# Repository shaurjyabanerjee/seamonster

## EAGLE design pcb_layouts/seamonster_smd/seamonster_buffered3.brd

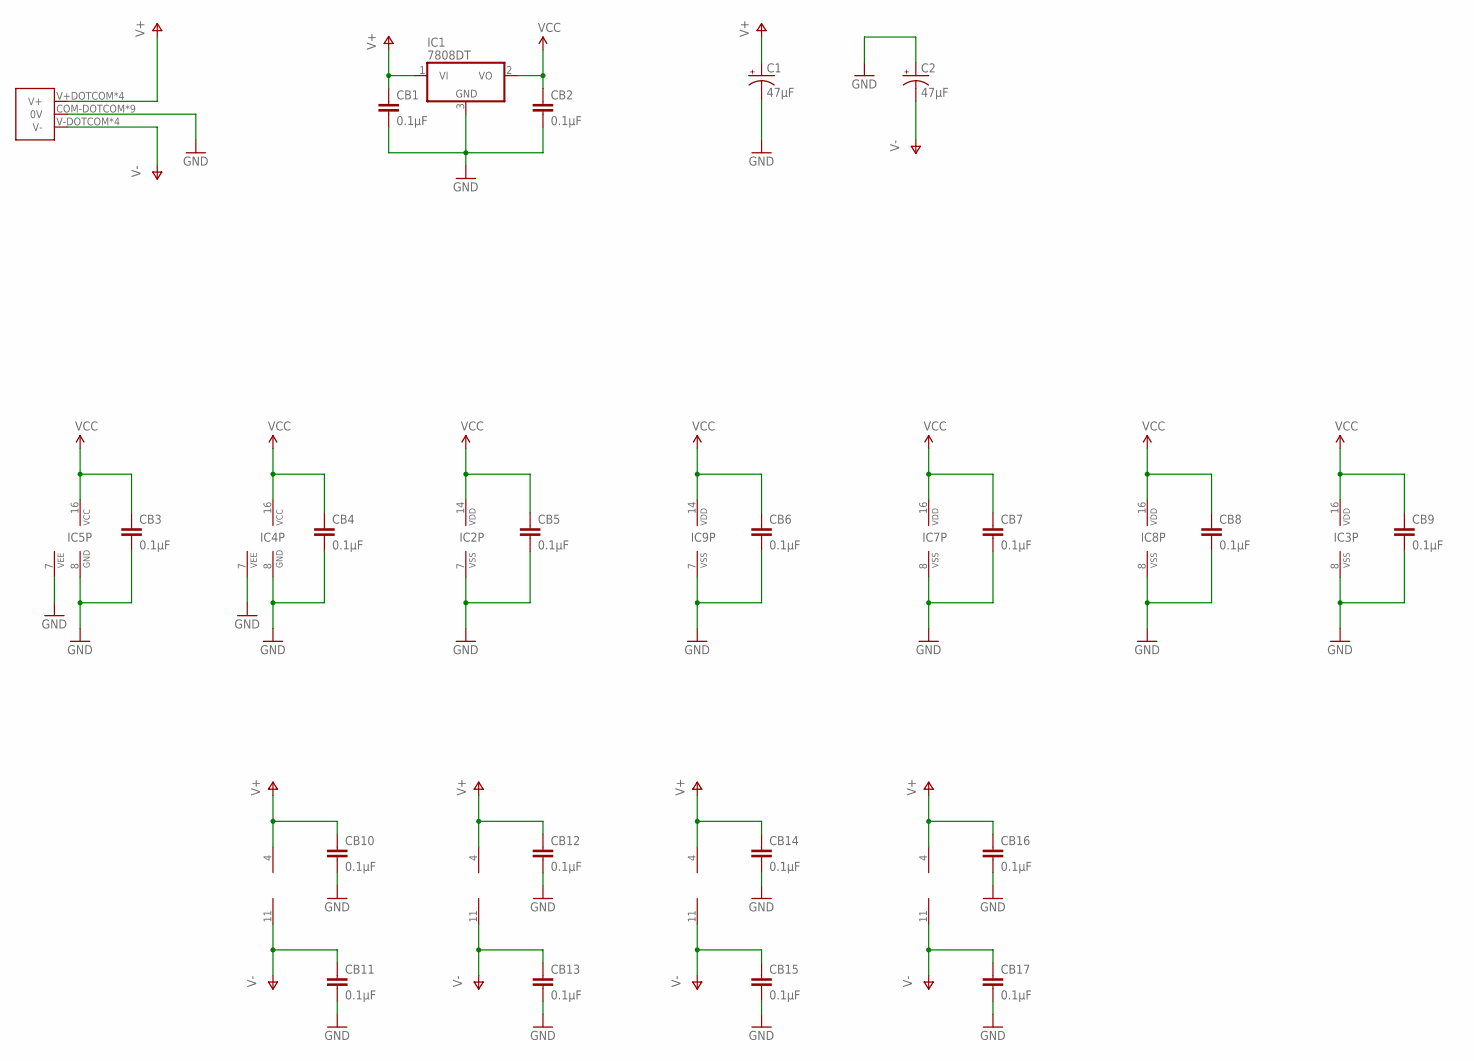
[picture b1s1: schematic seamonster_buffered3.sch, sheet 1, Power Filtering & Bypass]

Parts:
C1, C2: 47µF; CPOL-RADIAL-10UF-25V
CB1, CB2, CB3, CB4, CB5, CB6, CB7, CB8, CB9, CB10, CB11, CB12, CB13, CB14, CB15, CB16, CB17: 0.1µF; 0805
IC1: 7808DT; TO252
IC2: 40106D; SO14
IC3: 4040D; SO16
IC4, IC5: 4051D; SO16
IC7, IC8: 4046D; SO16
IC9: 4070D; SO14
U1, U2, U3: TL084; SO14
U4: TL084D; SO14
U$1: COMBO_POWER

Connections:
GND: C1.2 (-), C2.1 (+), CB1.2, CB2.2, CB3.2, CB4.2, CB5.2, CB6.2, CB7.2, CB8.2, CB9.2, CB10.2, CB11.2, CB12.2, CB13.2, CB14.2, CB15.2, CB16.2, CB17.2, IC1.3 (GND), IC2.7 (VSS), IC3.8 (VSS), IC4.7 (VEE), IC4.8 (GND), IC5.7 (VEE), IC5.8 (GND), IC7.8 (VSS), IC8.8 (VSS), IC9.7 (VSS), U$1.COM-DOTCOM (0V), U$1.COM-EURO1 (0V), U$1.COM-EURO2 (0V), U$1.COM-EURO3 (0V), U$1.COM-EURO4 (0V), U$1.COM-EURO5 (0V), U$1.COM-EURO6 (0V), U$1.COM-MOTM1 (0V), U$1.COM_MOTM2 (0V); also elsewhere on the board
V+: C1.1 (+), CB1.1, CB10.1, CB12.1, CB14.1, CB16.1, IC1.1 (VI), U1.4 (V+), U2.4 (V+), U3.4 (V+), U4.4 (V+), U$1.V+DOTCOM (V+), U$1.V+EURO1 (V+), U$1.V+EURO2 (V+), U$1.V+MOTM (V+); also elsewhere on the board
V-: C2.2 (-), CB11.1, CB13.1, CB15.1, CB17.1, U1.11 (V-), U2.11 (V-), U3.11 (V-), U4.11 (V-), U$1.V-DOTCOM (V-), U$1.V-EURO1 (V-), U$1.V-EURO2 (V-), U$1.V-MOTM (V-); also elsewhere on the board
VCC: CB2.1, CB3.1, CB4.1, CB5.1, CB6.1, CB7.1, CB8.1, CB9.1, IC1.2 (VO), IC2.14 (VDD), IC3.16 (VDD), IC4.16 (VCC), IC5.16 (VCC), IC7.16 (VDD), IC8.16 (VDD), IC9.14 (VDD); also elsewhere on the board

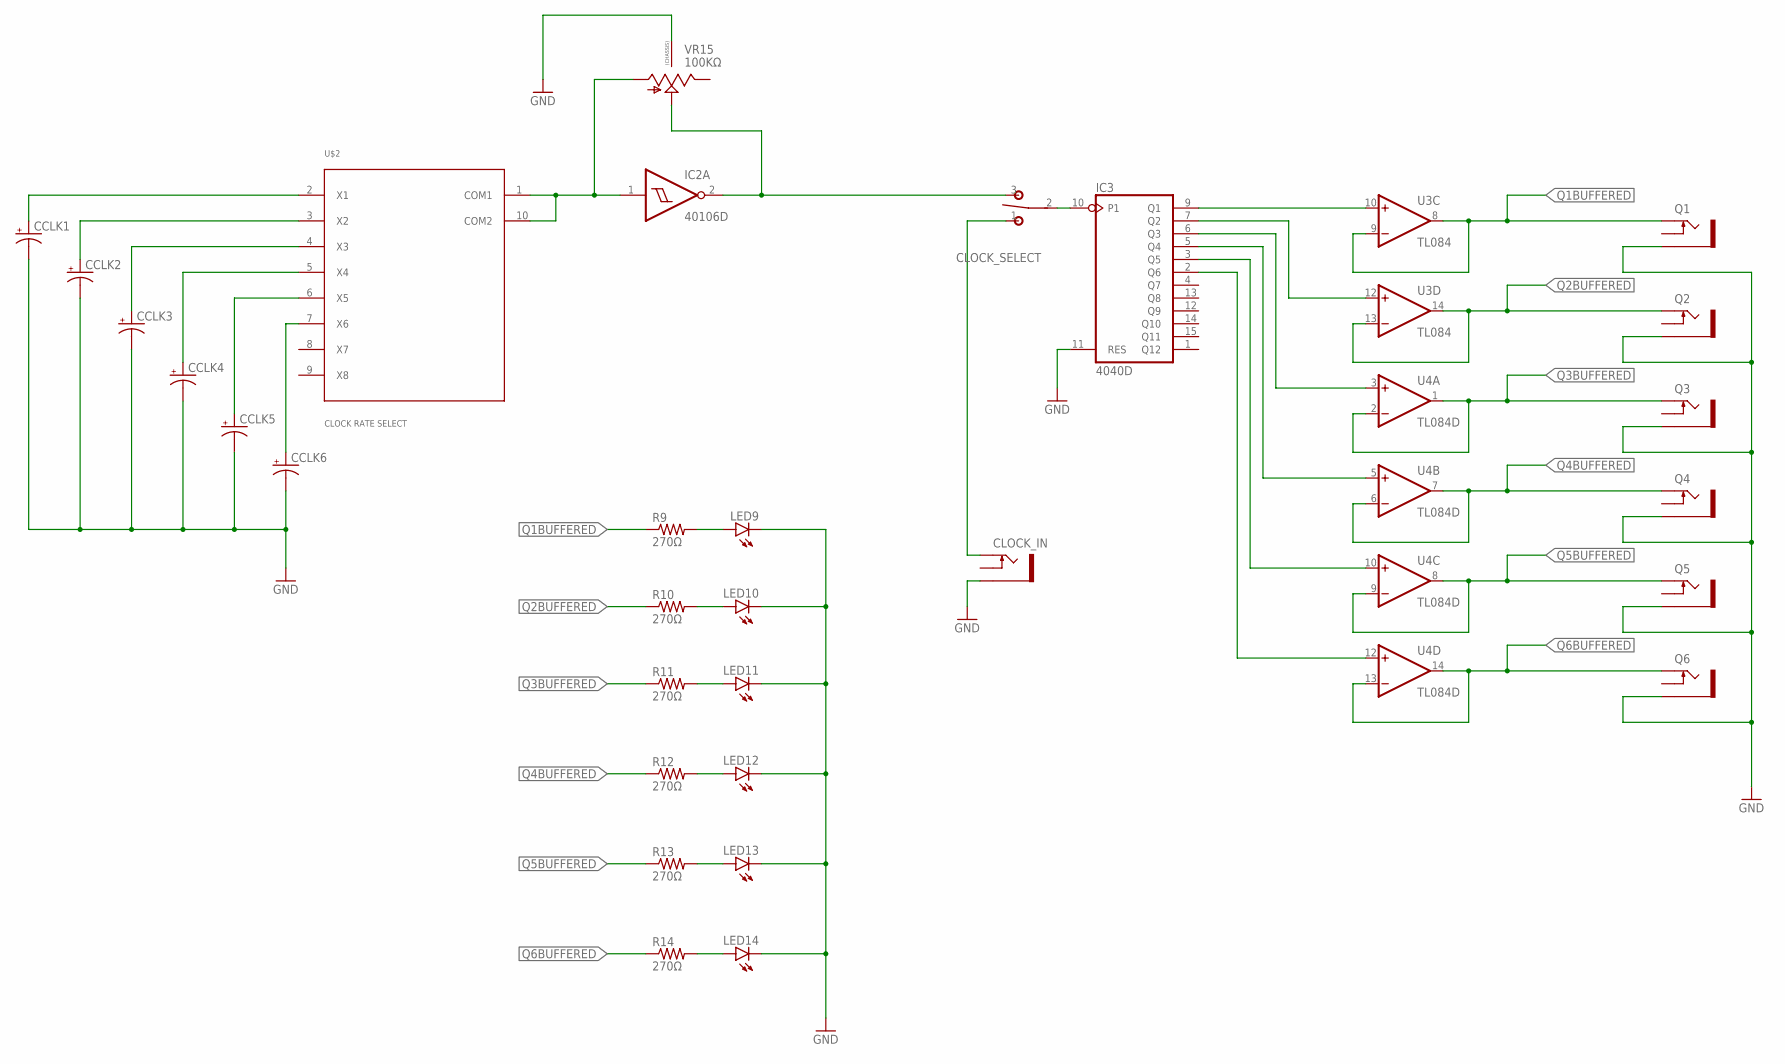
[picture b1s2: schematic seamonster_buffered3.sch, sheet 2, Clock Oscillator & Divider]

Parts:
CCLK1, CCLK2, CCLK3, CCLK4, CCLK5, CCLK6: 10UF-25V-20%(PTH); CPOL-RADIAL-10UF-25V
CLOCK_IN: THONKICONNNEW; WQP-PJ301M-12_JACK
CLOCK_SELECT: SPDT ON-ON; M9040P
IC2: 40106D; SO14
IC3: 4040D; SO16
LED9, LED10, LED11, LED12, LED13, LED14: LED3MM
Q1, Q2, Q3, Q4, Q5, Q6: THONKICONNNEW; WQP-PJ301M-12_JACK
R9, R10, R11, R12, R13, R14: 270Ω; 0805
U3: TL084; SO14
U4: TL084D; SO14
U$2: CLOCK RATE SELECT; ALPHA_SR1712F
VR15: 100KΩ; 9MM_SNAP-IN_POT

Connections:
GND: CCLK1.2 (-), CCLK2.2 (-), CCLK3.2 (-), CCLK4.2 (-), CCLK5.2 (-), CCLK6.2 (-), CLOCK_IN.P$3_SLEEVE (SLEEVE), IC3.11 (RES), LED9.K (C), LED10.K (C), LED11.K (C), LED12.K (C), LED13.K (C), LED14.K (C), Q1.P$3_SLEEVE (SLEEVE), Q2.P$3_SLEEVE (SLEEVE), Q3.P$3_SLEEVE (SLEEVE), Q4.P$3_SLEEVE (SLEEVE), Q5.P$3_SLEEVE (SLEEVE), Q6.P$3_SLEEVE (SLEEVE), VR15.CHASSIS2; also elsewhere on the board
unnamed: IC2.1 (I), U$2.1 (COM1), U$2.10 (COM2), VR15.1 (A)
unnamed: CCLK1.1 (+), U$2.2 (X1)
unnamed: CCLK2.1 (+), U$2.3 (X2)
unnamed: CCLK3.1 (+), U$2.4 (X3)
unnamed: CCLK4.1 (+), U$2.5 (X4)
unnamed: CCLK5.1 (+), U$2.6 (X5)
unnamed: CCLK6.1 (+), U$2.7 (X6)
unnamed: CLOCK_SELECT.3 (S), IC2.2 (O), VR15.2 (S)
unnamed: CLOCK_SELECT.2, IC3.10 (P1)
unnamed: LED9.A, R9.2
unnamed: IC3.9 (Q1), U3.10 (+IN)
unnamed: LED10.A, R10.2
unnamed: LED11.A, R11.2
unnamed: LED12.A, R12.2
unnamed: LED13.A, R13.2
unnamed: LED14.A, R14.2
unnamed: CLOCK_IN.P$1_TIP (TIP), CLOCK_SELECT.1 (O)
Q1BUFFERED: Q1.P$1_TIP (TIP), R9.1, U3.8 (OUT), U3.9 (-IN); also elsewhere on the board
Q2: IC3.7 (Q2), U3.12 (+IN)
Q2BUFFERED: Q2.P$1_TIP (TIP), R10.1, U3.13 (-IN), U3.14 (OUT); also elsewhere on the board
Q3: IC3.6 (Q3), U4.3 (+IN)
Q3BUFFERED: Q3.P$1_TIP (TIP), R11.1, U4.1 (OUT), U4.2 (-IN); also elsewhere on the board
Q4: IC3.5 (Q4), U4.5 (+IN)
Q4BUFFERED: Q4.P$1_TIP (TIP), R12.1, U4.6 (-IN), U4.7 (OUT)
Q5: IC3.3 (Q5), U4.10 (+IN)
Q5BUFFERED: Q5.P$1_TIP (TIP), R13.1, U4.8 (OUT), U4.9 (-IN)
Q6: IC3.2 (Q6), U4.12 (+IN)
Q6BUFFERED: Q6.P$1_TIP (TIP), R14.1, U4.13 (-IN), U4.14 (OUT)

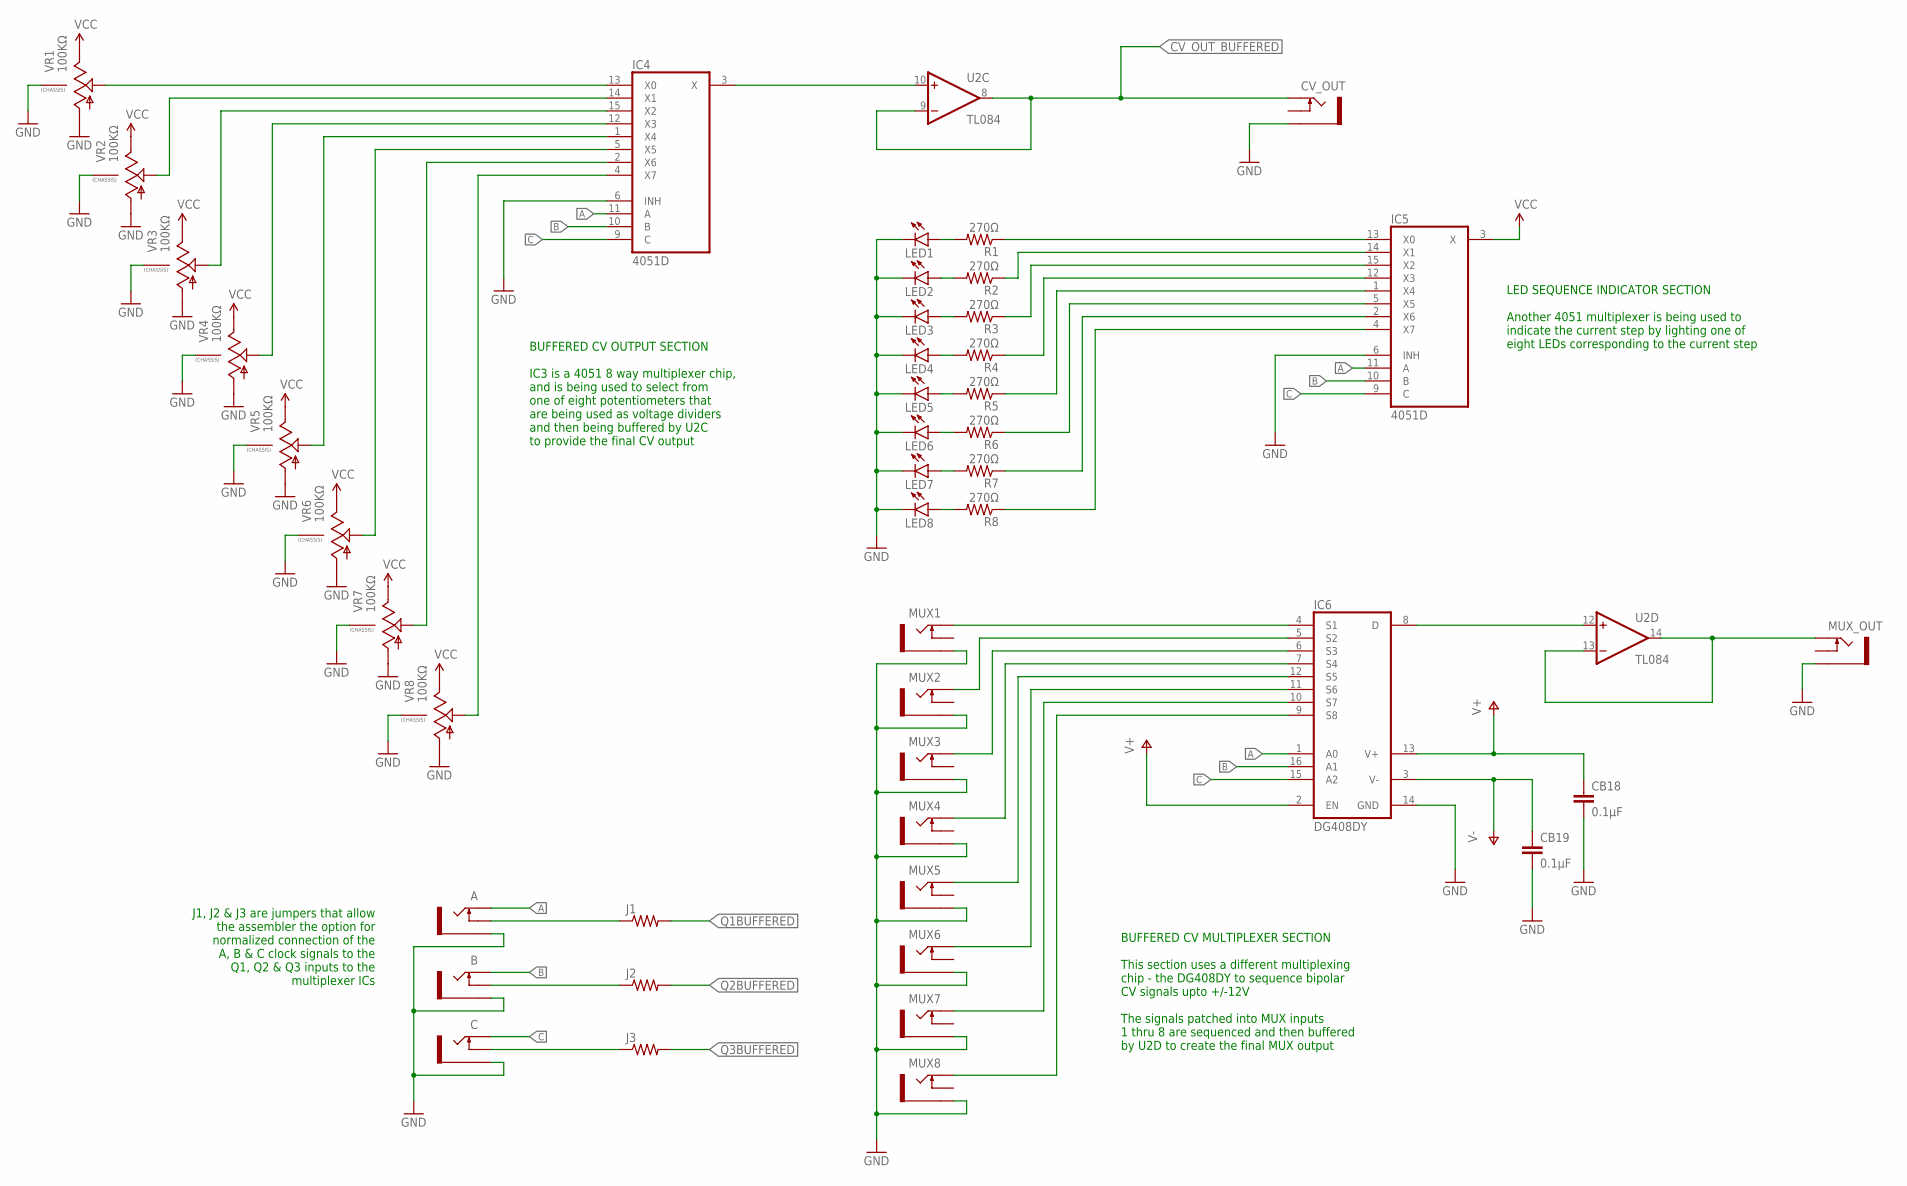
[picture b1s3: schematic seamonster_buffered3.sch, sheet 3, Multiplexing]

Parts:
A: THONKICONNNEW; WQP-PJ301M-12_JACK
B: THONKICONNNEW; WQP-PJ301M-12_JACK
C: THONKICONNNEW; WQP-PJ301M-12_JACK
CB18, CB19: 0.1µF; 0805
CV_OUT: THONKICONNNEW; WQP-PJ301M-12_JACK
IC4, IC5: 4051D; SO16
IC6: DG408DY; SO16
J1, J2, J3: RESISTOR0805-RES; 0805
LED1, LED2, LED3, LED4, LED5, LED6, LED7, LED8: LED3MM
MUX1, MUX2, MUX3, MUX4, MUX5, MUX6, MUX7, MUX8: THONKICONNNEW; WQP-PJ301M-12_JACK
MUX_OUT: THONKICONNNEW; WQP-PJ301M-12_JACK
R1, R2, R3, R4, R5, R6, R7, R8: 270Ω; 0805
U2: TL084; SO14
VR1, VR2, VR3, VR4, VR5, VR6, VR7, VR8: 100KΩ; 9MM_SNAP-IN_POT

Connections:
A: A.P$1_TIP (TIP), IC4.11 (A), IC5.11 (A), IC6.1 (A0)
B: B.P$1_TIP (TIP), IC4.10 (B), IC5.10 (B), IC6.16 (A1)
C: C.P$1_TIP (TIP), IC4.9 (C), IC5.9 (C), IC6.15 (A2)
CV_OUT: IC4.3 (X), U2.10 (+IN)
CV_OUT_BUFFERED: CV_OUT.P$1_TIP (TIP), U2.8 (OUT), U2.9 (-IN); also elsewhere on the board
GND: A.P$3_SLEEVE (SLEEVE), B.P$3_SLEEVE (SLEEVE), C.P$3_SLEEVE (SLEEVE), CB18.2, CB19.2, CV_OUT.P$3_SLEEVE (SLEEVE), IC4.6 (INH), IC5.6 (INH), IC6.14 (GND), LED1.K (C), LED2.K (C), LED3.K (C), LED4.K (C), LED5.K (C), LED6.K (C), LED7.K (C), LED8.K (C), MUX1.P$3_SLEEVE (SLEEVE), MUX2.P$3_SLEEVE (SLEEVE), MUX3.P$3_SLEEVE (SLEEVE), MUX4.P$3_SLEEVE (SLEEVE), MUX5.P$3_SLEEVE (SLEEVE), MUX6.P$3_SLEEVE (SLEEVE), MUX7.P$3_SLEEVE (SLEEVE), MUX8.P$3_SLEEVE (SLEEVE), MUX_OUT.P$3_SLEEVE (SLEEVE), VR1.1 (A), VR1.CHASSIS2, VR2.1 (A), VR2.CHASSIS2, VR3.1 (A), VR3.CHASSIS2, VR4.1 (A), VR4.CHASSIS2, VR5.1 (A), VR5.CHASSIS2, VR6.1 (A), VR6.CHASSIS2, VR7.1 (A), VR7.CHASSIS2, VR8.1 (A), VR8.CHASSIS2; also elsewhere on the board
MUX1: IC6.4 (S1), MUX1.P$1_TIP (TIP)
MUX2: IC6.5 (S2), MUX2.P$1_TIP (TIP)
MUX3: IC6.6 (S3), MUX3.P$1_TIP (TIP)
MUX4: IC6.7 (S4), MUX4.P$1_TIP (TIP)
MUX5: IC6.12 (S5), MUX5.P$1_TIP (TIP)
MUX6: IC6.11 (S6), MUX6.P$1_TIP (TIP)
MUX7: IC6.10 (S7), MUX7.P$1_TIP (TIP)
MUX8: IC6.9 (S8), MUX8.P$1_TIP (TIP)
unnamed: IC6.8 (D), U2.12 (+IN)
unnamed: MUX_OUT.P$1_TIP (TIP), U2.13 (-IN), U2.14 (OUT)
unnamed: LED1.A, R1.2
unnamed: LED2.A, R2.2
unnamed: LED3.A, R3.2
unnamed: LED4.A, R4.2
unnamed: LED5.A, R5.2
unnamed: LED6.A, R6.2
unnamed: LED7.A, R7.2
unnamed: LED8.A, R8.2
unnamed: IC4.13 (X0), VR1.2 (S)
unnamed: IC5.13 (X0), R1.1
unnamed: IC5.14 (X1), R2.1
unnamed: IC5.15 (X2), R3.1
unnamed: IC5.12 (X3), R4.1
unnamed: IC5.1 (X4), R5.1
unnamed: IC5.5 (X5), R6.1
unnamed: IC5.2 (X6), R7.1
unnamed: IC5.4 (X7), R8.1
unnamed: IC4.14 (X1), VR2.2 (S)
unnamed: IC4.15 (X2), VR3.2 (S)
unnamed: IC4.12 (X3), VR4.2 (S)
unnamed: IC4.1 (X4), VR5.2 (S)
unnamed: IC4.5 (X5), VR6.2 (S)
unnamed: IC4.2 (X6), VR7.2 (S)
unnamed: IC4.4 (X7), VR8.2 (S)
unnamed: A.P$2_SWITCH (SWITCH), J1.1
unnamed: B.P$2_SWITCH (SWITCH), J2.1
unnamed: C.P$2_SWITCH (SWITCH), J3.1
Q1BUFFERED: J1.2; also elsewhere on the board
Q2BUFFERED: J2.2; also elsewhere on the board
Q3BUFFERED: J3.2; also elsewhere on the board
V+: CB18.1, IC6.2 (EN), IC6.13 (V+); also elsewhere on the board
V-: CB19.1, IC6.3 (V-); also elsewhere on the board
VCC: IC5.3 (X), VR1.3 (E), VR2.3 (E), VR3.3 (E), VR4.3 (E), VR5.3 (E), VR6.3 (E), VR7.3 (E), VR8.3 (E); also elsewhere on the board

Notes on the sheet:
LED SEQUENCE INDICATOR SECTION Another 4051 multiplexer is being used to indicate the current step by lighting one of eight LEDs corresponding to the current step
J1, J2 & J3 are jumpers that allow the assembler the option for normalized connection of the A, B & C clock signals to the Q1, Q2 & Q3 inputs to the multiplexer ICs
BUFFERED CV OUTPUT SECTION IC3 is a 4051 8 way multiplexer chip, and is being used to select from one of eight potentiometers that are being used as voltage dividers and then being buffered by U2C to provide the final CV output
BUFFERED CV MULTIPLEXER SECTION This section uses a different multiplexing chip - the DG408DY to sequence bipolar CV signals upto +/-12V The signals patched into MUX inputs 1 thru 8 are sequenced and then buffered by U2D to create the final MUX output

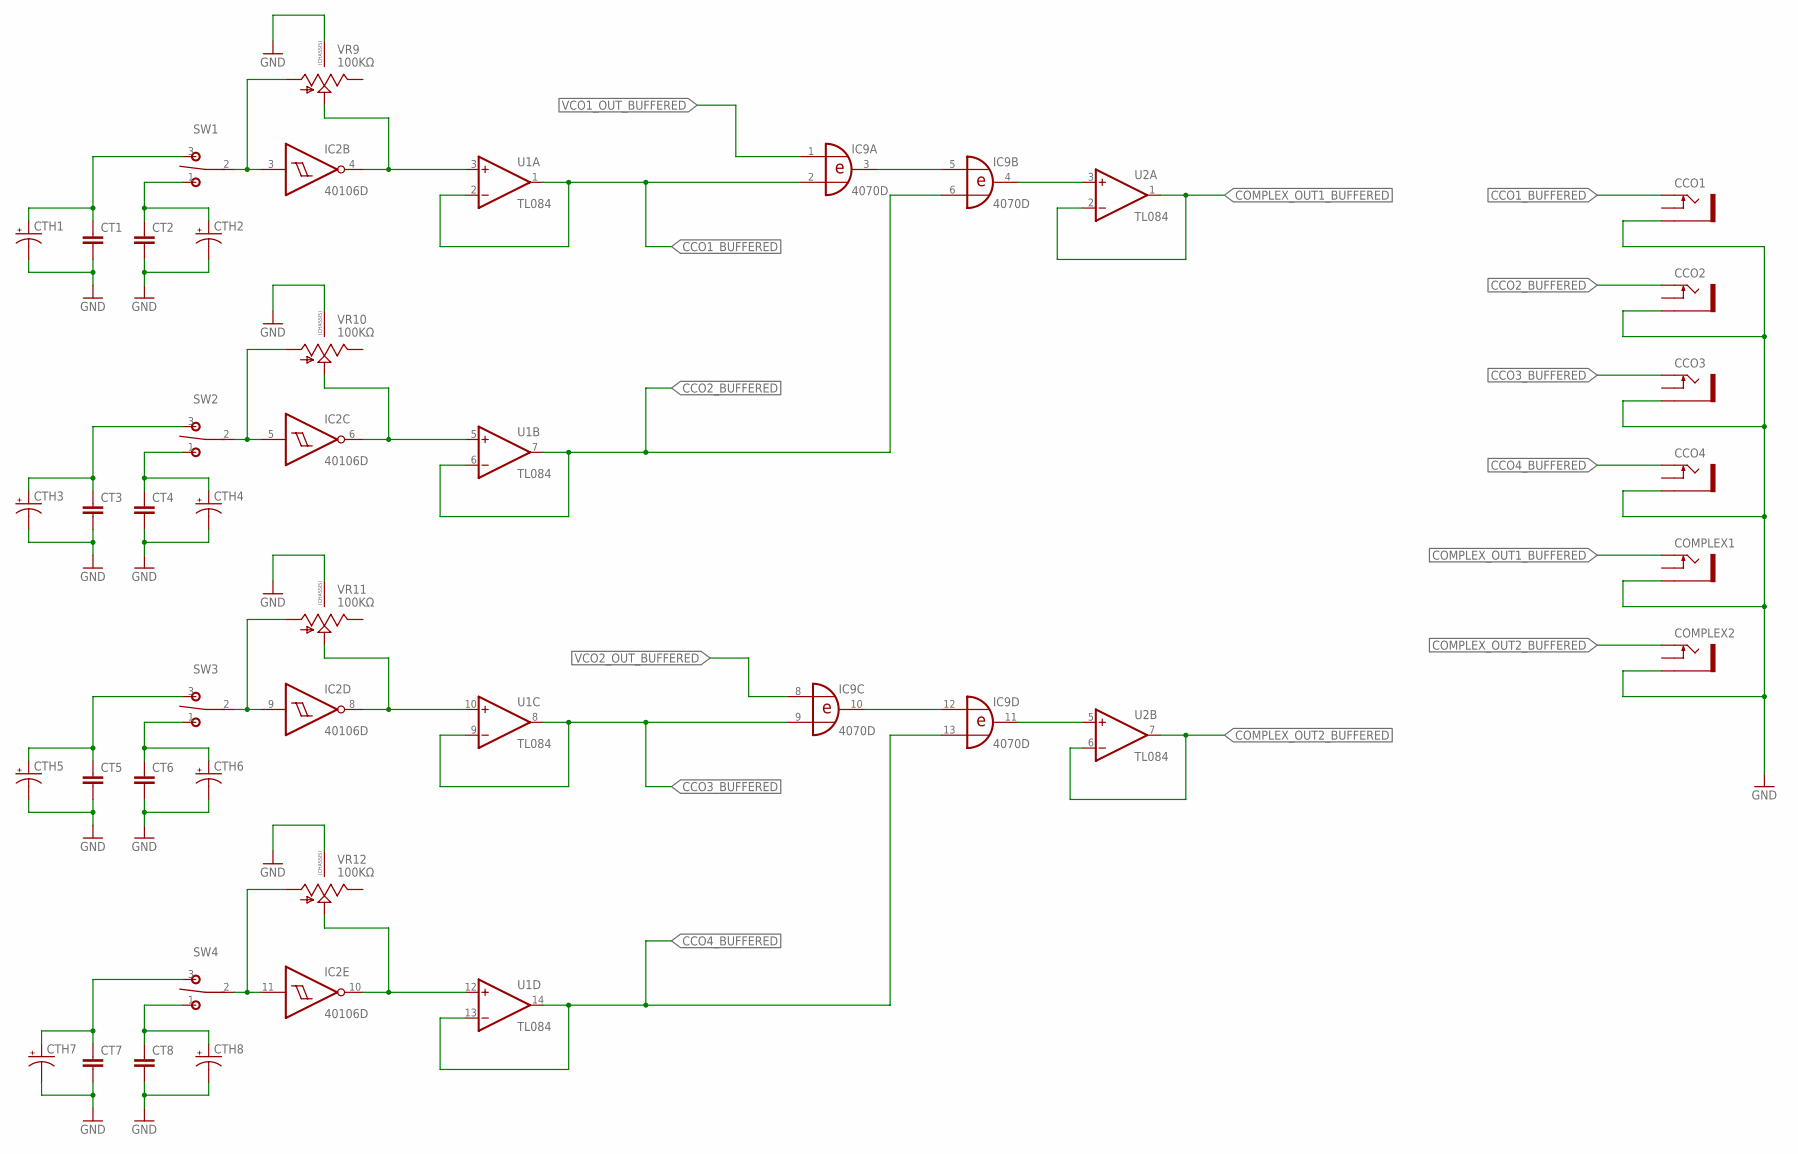
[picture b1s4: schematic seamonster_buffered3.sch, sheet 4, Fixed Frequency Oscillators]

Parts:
CCO1, CCO2, CCO3, CCO4: THONKICONNNEW; WQP-PJ301M-12_JACK
COMPLEX1, COMPLEX2: THONKICONNNEW; WQP-PJ301M-12_JACK
CT1, CT2, CT3, CT4, CT5, CT6, CT7, CT8: CAP0805; 0805
CTH1, CTH2, CTH3, CTH4, CTH5, CTH6, CTH7, CTH8: CAP_POLPTH2; CPOL-RADIAL-10UF-25V
IC2: 40106D; SO14
IC9: 4070D; SO14
SW1, SW2, SW3, SW4: SPDT ON-ON; M9040P
U1, U2: TL084; SO14
VR9, VR10, VR11, VR12: 100KΩ; 9MM_SNAP-IN_POT

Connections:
CCO1_BUFFERED: CCO1.P$1_TIP (TIP), IC9.2 (I1), U1.1 (OUT), U1.2 (-IN)
CCO2_BUFFERED: CCO2.P$1_TIP (TIP), IC9.6 (I1), U1.6 (-IN), U1.7 (OUT)
CCO3_BUFFERED: CCO3.P$1_TIP (TIP), IC9.9 (I1), U1.8 (OUT), U1.9 (-IN)
CCO4_BUFFERED: CCO4.P$1_TIP (TIP), IC9.13 (I1), U1.13 (-IN), U1.14 (OUT)
COMPLEX_OUT1_BUFFERED: COMPLEX1.P$1_TIP (TIP), U2.1 (OUT), U2.2 (-IN)
COMPLEX_OUT2_BUFFERED: COMPLEX2.P$1_TIP (TIP), U2.6 (-IN), U2.7 (OUT)
GND: CCO1.P$3_SLEEVE (SLEEVE), CCO2.P$3_SLEEVE (SLEEVE), CCO3.P$3_SLEEVE (SLEEVE), CCO4.P$3_SLEEVE (SLEEVE), COMPLEX1.P$3_SLEEVE (SLEEVE), COMPLEX2.P$3_SLEEVE (SLEEVE), CT1.2, CT2.2, CT3.2, CT4.2, CT5.2, CT6.2, CT7.2, CT8.2, CTH1.2 (-), CTH2.2 (-), CTH3.2 (-), CTH4.2 (-), CTH5.2 (-), CTH6.2 (-), CTH7.2 (-), CTH8.2 (-), VR9.CHASSIS2, VR10.CHASSIS2, VR11.CHASSIS2, VR12.CHASSIS2; also elsewhere on the board
INV_B_IN: IC2.3 (I), SW1.2, VR9.1 (A)
INV_B_OUT: IC2.4 (O), U1.3 (+IN), VR9.2 (S)
INV_C_IN: IC2.5 (I), SW2.2, VR10.1 (A)
INV_C_OUT: IC2.6 (O), U1.5 (+IN), VR10.2 (S)
INV_D_IN: IC2.9 (I), SW3.2, VR11.1 (A)
INV_D_OUT: IC2.8 (O), U1.10 (+IN), VR11.2 (S)
INV_E_IN: IC2.11 (I), SW4.2, VR12.1 (A)
INV_E_OUT: IC2.10 (O), U1.12 (+IN), VR12.2 (S)
unnamed: IC9.3 (O), IC9.5 (I0)
unnamed: IC9.10 (O), IC9.12 (I0)
unnamed: IC9.4 (O), U2.3 (+IN)
unnamed: IC9.11 (O), U2.5 (+IN)
unnamed: CT2.1, CTH2.1 (+), SW1.1 (O)
unnamed: CT1.1, CTH1.1 (+), SW1.3 (S)
unnamed: CT4.1, CTH4.1 (+), SW2.1 (O)
unnamed: CT3.1, CTH3.1 (+), SW2.3 (S)
unnamed: CT6.1, CTH6.1 (+), SW3.1 (O)
unnamed: CT5.1, CTH5.1 (+), SW3.3 (S)
unnamed: CT8.1, CTH8.1 (+), SW4.1 (O)
unnamed: CT7.1, CTH7.1 (+), SW4.3 (S)
VCO1_OUT_BUFFERED: IC9.1 (I0); also elsewhere on the board
VCO2_OUT_BUFFERED: IC9.8 (I0); also elsewhere on the board

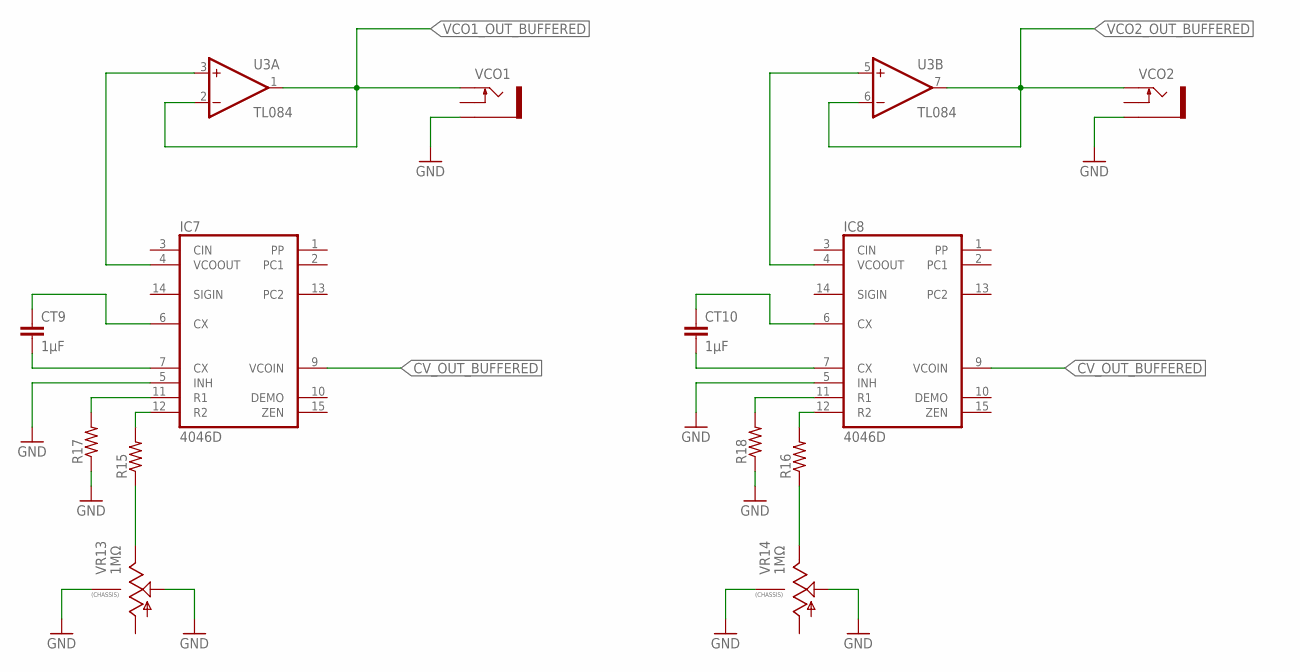
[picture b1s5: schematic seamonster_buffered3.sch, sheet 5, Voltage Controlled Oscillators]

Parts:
CT9, CT10: 1µF; 0805
IC7, IC8: 4046D; SO16
R15, R16, R17, R18: RESISTOR0805-RES; 0805
U3: TL084; SO14
VCO1, VCO2: THONKICONNNEW; WQP-PJ301M-12_JACK
VR13, VR14: 1MΩ; 9MM_SNAP-IN_POT

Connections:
CV_OUT_BUFFERED: IC7.9 (VCOIN), IC8.9 (VCOIN); also elsewhere on the board
GND: IC7.5 (INH), IC8.5 (INH), R17.1, R18.1, VCO1.P$3_SLEEVE (SLEEVE), VCO2.P$3_SLEEVE (SLEEVE), VR13.2 (S), VR13.CHASSIS2, VR14.2 (S), VR14.CHASSIS2; also elsewhere on the board
unnamed: IC7.12 (R2), R15.2
unnamed: R15.1, VR13.3 (E)
unnamed: CT9.1, IC7.6 (CX)
unnamed: CT9.2, IC7.7 (CX)
unnamed: CT10.1, IC8.6 (CX)
unnamed: CT10.2, IC8.7 (CX)
unnamed: IC8.12 (R2), R16.2
unnamed: R16.1, VR14.3 (E)
unnamed: IC8.11 (R1), R18.2
unnamed: IC7.11 (R1), R17.2
VCO1_OUT: IC7.4 (VCOOUT), U3.3 (+IN)
VCO1_OUT_BUFFERED: U3.1 (OUT), U3.2 (-IN), VCO1.P$1_TIP (TIP); also elsewhere on the board
VCO2_OUT: IC8.4 (VCOOUT), U3.5 (+IN)
VCO2_OUT_BUFFERED: U3.6 (-IN), U3.7 (OUT), VCO2.P$1_TIP (TIP); also elsewhere on the board

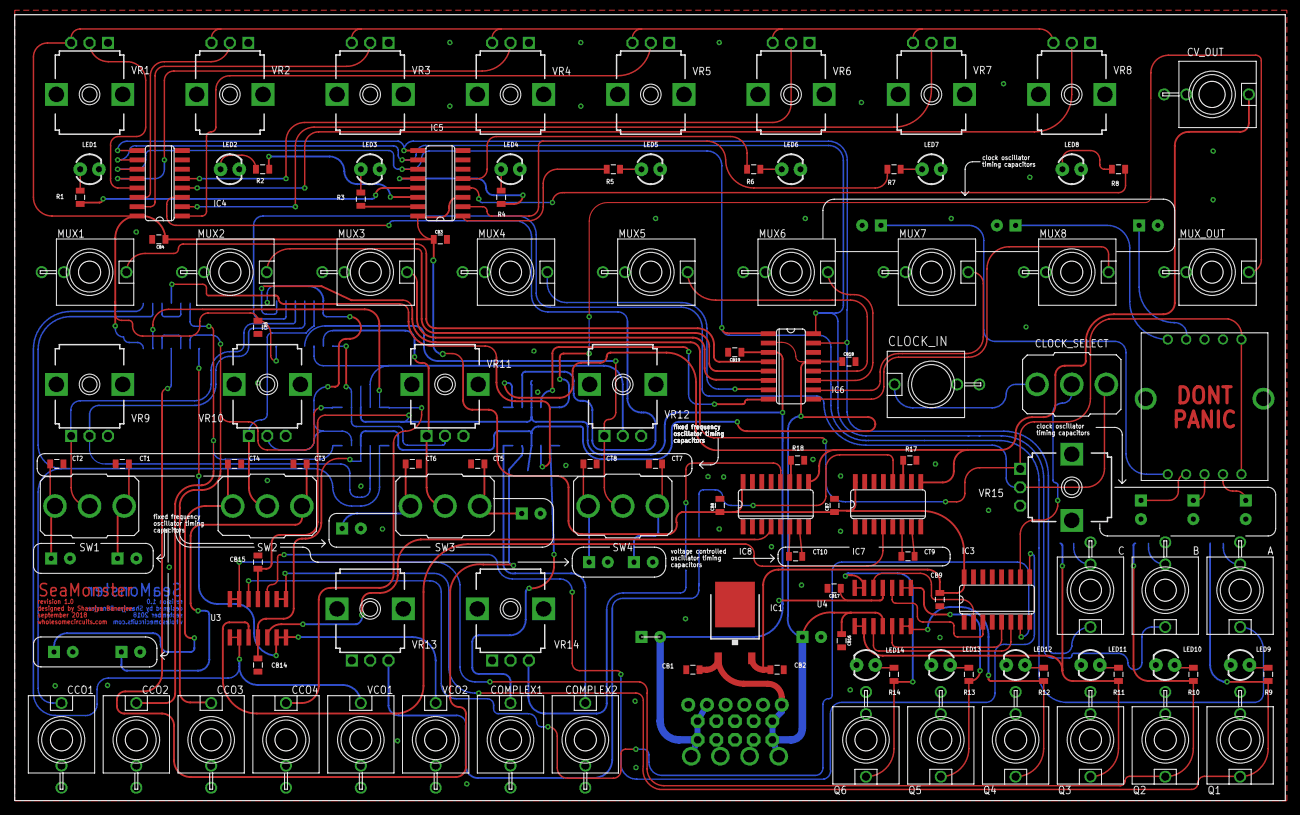
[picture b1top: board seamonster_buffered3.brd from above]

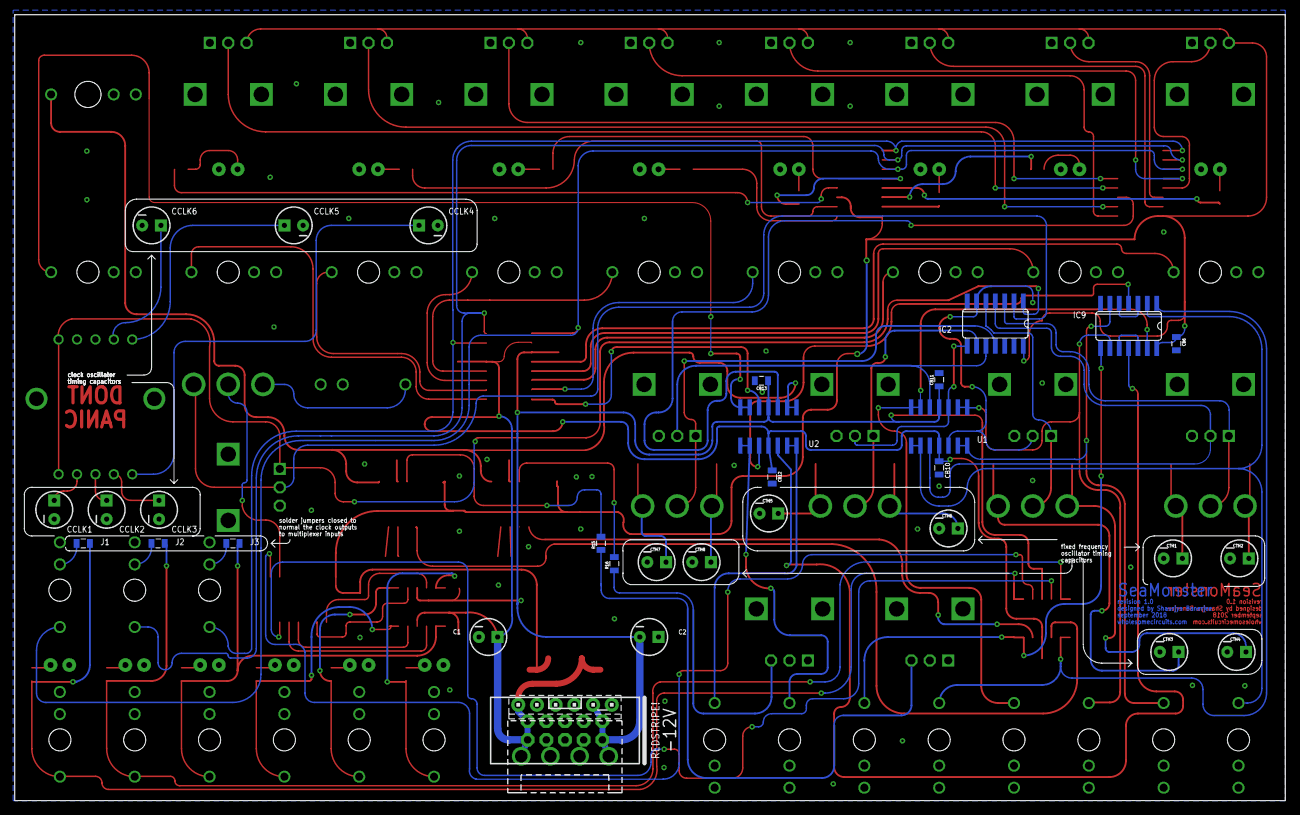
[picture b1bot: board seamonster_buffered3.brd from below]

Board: 2 copper layers, 172.5 x 106.7 mm, 143 parts (31 on the bottom side), 114 nets.

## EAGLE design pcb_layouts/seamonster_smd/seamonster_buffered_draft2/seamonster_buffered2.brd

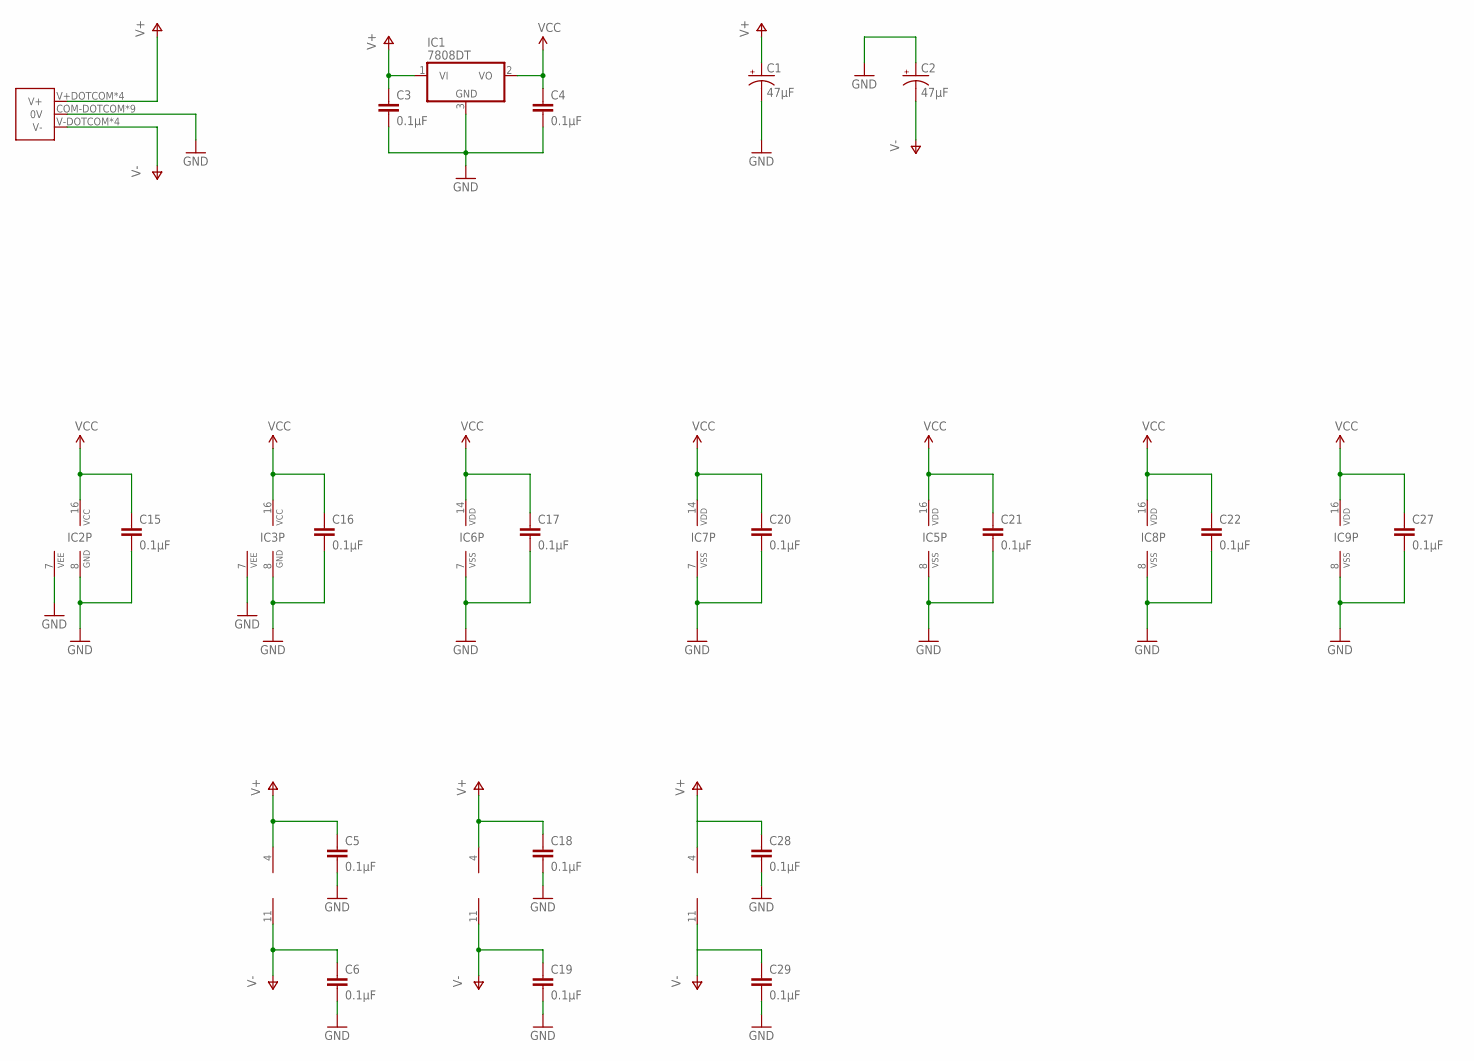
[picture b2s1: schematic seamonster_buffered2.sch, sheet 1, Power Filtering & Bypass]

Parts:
C1, C2: 47µF; CPOL-RADIAL-10UF-25V
C3, C4, C5, C6, C15, C16, C17, C18, C19, C20, C21, C22, C27, C28, C29: 0.1µF; 0805
IC1: 7808DT; TO252
IC2, IC3: 4051D; SO16
IC5, IC8: 4046D; SO16
IC6: 40106D; SO14
IC7: 4070D; SO14
IC9: 4040D; SO16
U1, U2, U3: TL084; SO14
U$1: COMBO_POWER

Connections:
V+: C1.1 (+), C3.1, C5.1, C18.1, C28.1, IC1.1 (VI), U1.4 (V+), U2.4 (V+), U3.4 (V+), U$1.V+DOTCOM (V+), U$1.V+EURO1 (V+), U$1.V+EURO2 (V+), U$1.V+MOTM (V+); also elsewhere on the board
V-: C2.2 (-), C6.1, C19.1, C29.1, U1.11 (V-), U2.11 (V-), U3.11 (V-), U$1.V-DOTCOM (V-), U$1.V-EURO1 (V-), U$1.V-EURO2 (V-), U$1.V-MOTM (V-); also elsewhere on the board
VCC: C4.1, C15.1, C16.1, C17.1, C20.1, C21.1, C22.1, C27.1, IC1.2 (VO), IC2.16 (VCC), IC3.16 (VCC), IC5.16 (VDD), IC6.14 (VDD), IC7.14 (VDD), IC8.16 (VDD), IC9.16 (VDD); also elsewhere on the board

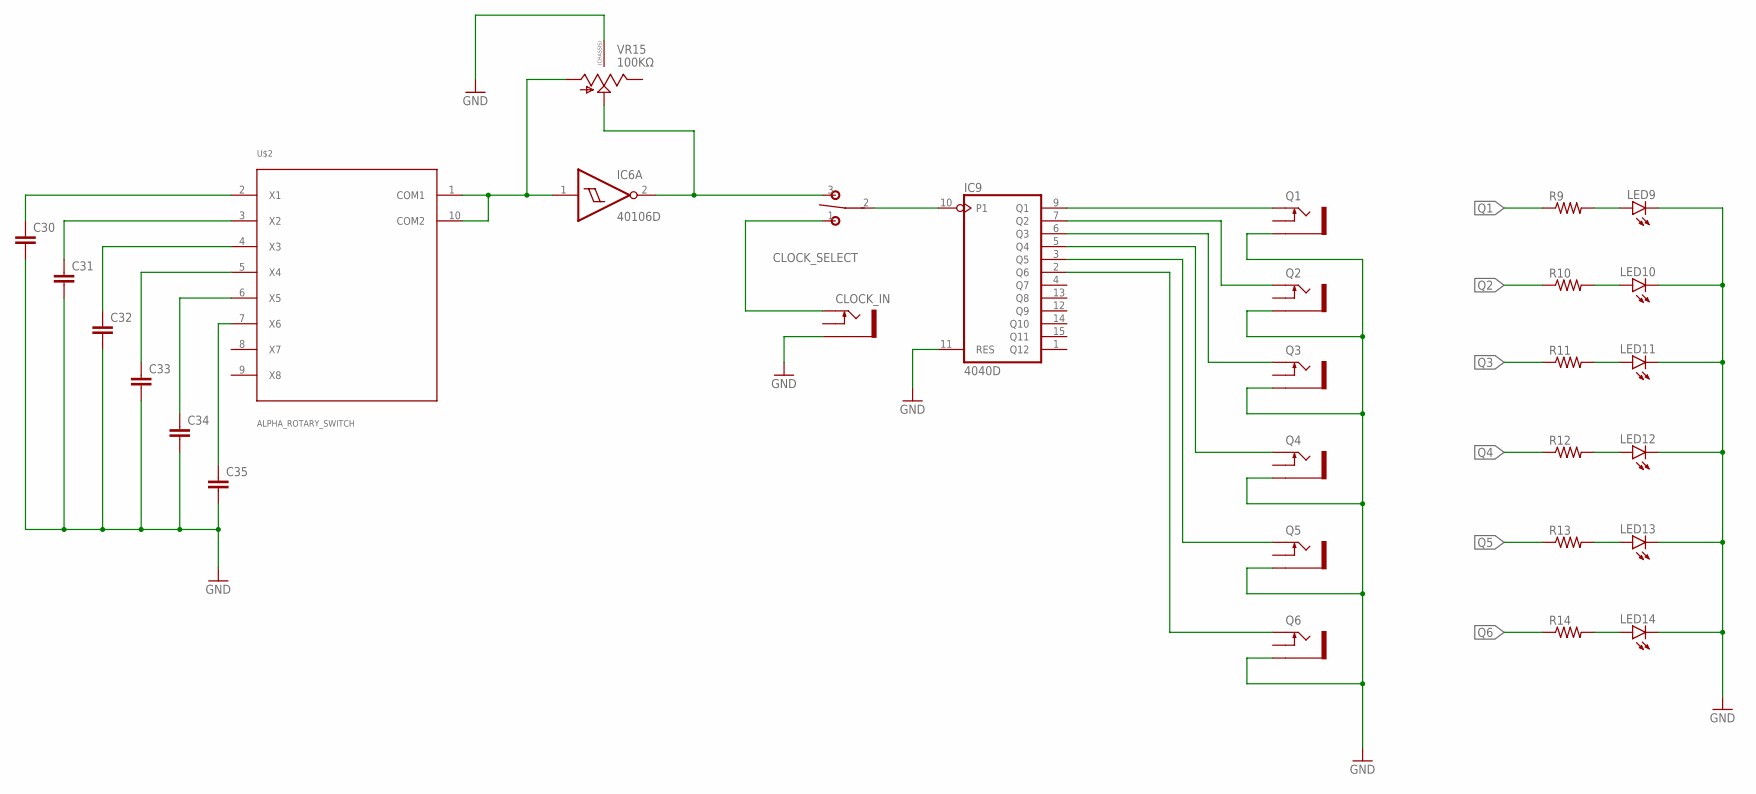
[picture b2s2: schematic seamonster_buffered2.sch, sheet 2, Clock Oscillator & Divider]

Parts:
C30, C31, C32, C33, C34, C35: CAP0805; 0805
CLOCK_IN: THONKICONNNEW; WQP-PJ301M-12_JACK
CLOCK_SELECT: SPDT ON-ON; M9040P
IC6: 40106D; SO14
IC9: 4040D; SO16
LED9, LED10, LED11, LED12, LED13, LED14: LED3MM
Q1, Q2, Q3, Q4, Q5, Q6: THONKICONNNEW; WQP-PJ301M-12_JACK
R9, R10, R11, R12, R13, R14: RESISTOR0805-RES; 0805
U$2: ALPHA_ROTARY_SWITCH; ALPHA_SR1712F
VR15: 100KΩ; 9MM_SNAP-IN_POT

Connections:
unnamed: IC6.1 (I), U$2.1 (COM1), U$2.10 (COM2), VR15.1 (A)
unnamed: C30.1, U$2.2 (X1)
unnamed: C31.1, U$2.3 (X2)
unnamed: C32.1, U$2.4 (X3)
unnamed: C33.1, U$2.5 (X4)
unnamed: C34.1, U$2.6 (X5)
unnamed: C35.1, U$2.7 (X6)
unnamed: CLOCK_SELECT.3 (S), IC6.2 (O), VR15.2 (S)
unnamed: CLOCK_SELECT.2, IC9.10 (P1)
unnamed: LED9.A, R9.2
unnamed: LED10.A, R10.2
unnamed: LED11.A, R11.2
unnamed: LED12.A, R12.2
unnamed: LED13.A, R13.2
unnamed: LED14.A, R14.2
unnamed: CLOCK_IN.P$1_TIP (TIP), CLOCK_SELECT.1 (O)
Q1: IC9.9 (Q1), Q1.P$1_TIP (TIP), R9.1; also elsewhere on the board
Q2: IC9.7 (Q2), Q2.P$1_TIP (TIP), R10.1; also elsewhere on the board
Q3: IC9.6 (Q3), Q3.P$1_TIP (TIP), R11.1; also elsewhere on the board
Q4: IC9.5 (Q4), Q4.P$1_TIP (TIP), R12.1
Q5: IC9.3 (Q5), Q5.P$1_TIP (TIP), R13.1
Q6: IC9.2 (Q6), Q6.P$1_TIP (TIP), R14.1

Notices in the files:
parts and their libraries:
SparkFun-Capacitors: Licensing: Creative Commons ShareAlike 4.0 International - https://creativecommons.org/licenses/by-sa/4.0
